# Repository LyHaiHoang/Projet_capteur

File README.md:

# Projet : Capteur Graphite à Crayon

## Table des matières
- [Projet : Capteur Graphite à Crayon](#projet--capteur-graphite-à-crayon)
  - [Table des matières](#table-des-matières)
- [Contexte](#contexte)
- [Réalisation du projet](#réalisation-du-projet)
  - [1. Matériaux utilisés](#1-matériaux-utilisés)
  - [2. Simulation électronique en utilisant LTSpice](#2-simulation-électronique-en-utilisant-ltspice)
    - [2.1 Fonctionnalité de condition nominale](#21-fonctionnalité-de-condition-nominale)
    - [2.2 Modélisation du capteur](#22-modélisation-du-capteur)
    - [2.3 Résultats visuels](#23-résultats-visuels)
    - [2.4 Simulation du signal alternatif](#24-simulation-du-signal-alternatif)
  - [3. Conception du circuit PCB en utilisant KiCad](#3-conception-du-circuit-pcb-en-utilisant-kicad)
    - [3.1 Réalisation des symboles et empreintes](#31-réalisation-des-symboles-et-empreintes)
    - [3.2 Réalisation du schéma électronique](#32-réalisation-du-schéma-électronique)
    - [3.3 Réalisation du PCB](#33-réalisation-du-pcb)
  - [4. Code Arduino](#4-code-arduino)
  - [5. Application Android codée avec MIT App Inventor](#5-application-android-codée-avec-mit-app-inventor)
    - [5.1. Initialisation](#51-initialisation)
    - [5.2. Composantes dans l'interface](#52-composantes-dans-linterface)
      - [Connection du Bluetooth:](#connection-du-bluetooth)
    - [Le bouton pour le capteur industriel (FlexSensor) et le capteur graphite](#le-bouton-pour-le-capteur-industriel-flexsensor-et-le-capteur-graphite)
    - [Le bouton "Mesure"](#le-bouton-mesure)
    - [Le bouton "Reset"](#le-bouton-reset)
    - [Bloc principal - Timer](#bloc-principal---timer)
    - [Le Graphique](#le-graphique)
  - [6. Réalisation du Shield](#6-réalisation-du-shield)
  - [7. Banc de test](#7-banc-de-test)
    - [7.1 Physique derrière le capteur en graphite](#71-physique-derrière-le-capteur-en-graphite)
    - [7.2 Résultats de mesures](#72-résultats-de-mesures)
  - [8. Datasheet](#8-datasheet)
- [Conclusion](#conclusion)
- [Références](#références)
- [Contacts](#contacts)
  - [Étudiants](#étudiants)
  - [Enseignants](#enseignants)

---

# Contexte
Ce projet vise à développer un capteur basé sur du graphite de crayon de papier pour des applications en instrumentation. L'objectif est d'explorer les propriétés conductrices du graphite et de les exploiter dans un circuit électronique interactif.

---

# Réalisation du projet

---

## 1. Matériaux utilisés

Dans ce projet, nous utilisons des composants électroniques et des modules disponibles dans la salle d'instrumentation avec une carte Arduino UNO. Tous les composants sont listés ci-dessous :
   * 1 carte Arduino UNO Rev 3
   * 1 module Bluetooth (HC-05)
   * 1 encodeur rotatif (Keyes KY-040)
   * 1 écran OLED (SSD 1306)
   * 1 capteur de flexion commercial (LLC 1070)
   * 1 capteur en graphite fait à l'aide de la mine d'un crayon de papier
   * 1 amplificateur de transimpédance (LTC1050)
   * 1 potentiomètre numérique (MCP41100)
   * 2 supports IC pour le potentiomètre et l'amplificateur
   * 1 résistance 1kΩ, 1 résistance 10kΩ, 2 résistances 100kΩ
   * 3 condensateurs 100nF, 1 condensateur 1µF

---

## 2. Simulation électronique en utilisant LTSpice

### 2.1 Fonctionnalité de condition nominale

Le courant d’entrée Isens varie entre 50 nA et 100 nA, ce qui entraîne une variation de la tension Vep appliquée à l’entrée non-inverseur V+ du LTC1050, entre 5 mV et 10 mV.

Le gain de l’amplificateur du LTC1050 est défini par : G = 1 + R3/R2 = 101. Par conséquent, la valeur de la tension de sortie du LTC1050 varie entre 0.5 V et 1 V.

Au départ, le signal exprimé en décibels est de 140 dB, ce qui correspond à :  
20 log(VADC / Isens).

Le microcontrôleur utilisé est un Arduino UNO, basé sur un microcontrôleur AVR avec une fréquence d’échantillonnage maximale fech = 200 kHz.  
Comme la conversion analogique-numérique se fait sur 13 bits, la fréquence d’échantillonnage réelle est limitée à 15.4 kHz.

D'après le théorème de Nyquist, la fréquence maximale du signal que l'on peut correctement numériser doit donc être inférieure à la moitié de cette valeur :  
fsignal < fech/2 = 7.7 kHz.

### 2.2 Modélisation du capteur

Le bruit à 50 Hz, généré notamment par l'écran TFT (bruit de type secteur), est clairement observé dans le spectre du signal. Pour l’atténuer, on agit sur le condensateur C4 du filtre passe-bas.

- Lorsque la valeur de C4 est augmentée à 10 µF, le pic de bruit à 50 Hz est fortement réduit, ce qui indique une amélioration de l’atténuation dans les basses fréquences.

- En revanche, si on diminue la valeur de C4, le bruit augmente, montrant que la fréquence de coupure du filtre remonte et que le bruit secteur passe plus facilement.

### 2.3 Résultats visuels

Une photo démontrant que notre circuit permet une amplification efficace du signal délivré par le capteur :

### 2.4 Simulation du signal alternatif

Ensuite, on présente la réponse du circuit lorsque l'on simule un courant alternatif, afin de vérifier que le bruit est correctement filtré :

Le bruit du réseau est atténué d'environ 72 dB à 50 Hz.

---

## 3. Conception du circuit PCB en utilisant KiCad

Afin de concevoir le circuit électronique, le logiciel en libre accès KICAD a été utilisé. L'ensemble des fichiers KiCad est disponible dans le dossier [Capteur_KICAD](./Capteur_KICAD).

### 3.1 Réalisation des symboles et empreintes

Pour commencer notre PCB (Printed Circuit Board), il est nécessaire de créer les symboles et les empreintes des composants qui ne sont pas disponibles dans la bibliothèque de KiCad. Nous avons réalisé les symboles du module Bluetooth, de l'encodeur rotatif, de l'écran OLED, du capteur de flexion et du capteur en graphite, afin de les ajouter au schéma de connexion. Ensuite, ces symboles ont été associés à une empreinte trouvée sur des sites de libre téléchargement.

### 3.2 Réalisation du schéma électronique

Ensuite, le schéma électronique est à construire. Dans cette partie, les différentes connexions entre composants sont définies et les pins de la carte Arduino sont attribués à chacun des composants.

### 3.3 Réalisation du PCB

L'objectif ici était d'allouer un branchement sur les entrées d'une carte Arduino UNO à chaque module. Nous avons aussi pour but de faire le moins possible de via (pont traversant permettant de chavaucher un routage).
Le circuit imprimé a été dessiné avec une attention particulière portée à la disposition des pistes pour minimiser les couplages parasites et faciliter le routage manuel.

Les contraintes de branchement ont été les suivantes:
  * Encoder: pin clk -> pin 2 (Arduino)
  * Bluetooth: pin TXD -> la pin 5 (pin RXD de l'Arduino)
               pin RXD -> la pin 6 (pin TXD de l'Arduino)
  * Potentiomètre digital: pin SCK -> pin 13 (pin SCK de l'Arduino)
                           pin SDI -> pin 11 ()
  * FlexSensor: sur une pin analogue (A2 choisi)
  * Capteur Graphite: sur une pin analogue (A0 choisi)

Ensuite, l'impression du circuit s'est ensuite faite par méthode chimie:
  * Plaque de cuivre/résine dont la face en cuivre est enduite d'une résine photosensible;
  * Insolation de la résine sur les parties du cuivre non voulue;
  * Attaque chimique dans un bain révélateur;
  * Rinçage du circuit;

---

## 4. Code Arduino

Le code Arduino permet de lire les valeurs du capteur en graphite, de gérer l'affichage d'un Menu sur l'écran OLED, la communication par Bluetooth avec l'application Android (voir section [5. Application Android codée avec MIT App Inventor](#5.-Application-Android-codée-avec-MIT-App-Inventor)) et le contrôle via l'encodeur rotatif.
Le code arduino est disponible dans le dossier [Capteur_Arduino](./Capteur_Arduino).

---

## 5. Application Android codée avec MIT App Inventor

Une application mobile a été développée pour :
- Recevoir les données en Bluetooth,
- Afficher les mesures en temps réel,
- Interagir avec le capteur de manière intuitive.

### 5.1. Initialisation

  Nous avons déclaré les variables initiales utilisées dans le programme:

  Puis nous avons initialisé le programme:

### 5.2. Composantes dans l'interface
---
#### Connection du Bluetooth:

Le bouton « List_Connection » permet de sélectionner le module Bluetooth auquel on souhaite se connecter. Le bouton « Button_Disconnect » permet également de déconnecter le module Bluetooth sélectionné.

---

### Le bouton pour le capteur industriel (FlexSensor) et le capteur graphite

Ces bouton permet de choisir le capteur que l'on veut afficher leur valeurs.

---
### Le bouton "Mesure"

Ce bouton permet d'envoyer un message vers l'arduino via bluetooth pour lui demande de renvoyer les valeurs de resistances dependant le mode du capteur choisi.

---
### Le bouton "Reset"

Ce bouton permet de réinitialiser le graph.

---
### Bloc principal - Timer

Pour pouvoir récupérer automatiquement des données, on commande séquentiellement Arduino de nous evoyer les données. Pour cela, on utilise le composante "Clock"dans MIT. 

---
### Le Graphique

Le graphique montre le variation de résistance du capteur FlexSensor et du capteur graphite à chaque mesure.

## 6. Réalisation du Shield

Pour la réalisation du shield, nous avons manuellement soudé l'ensemble des modules arduino et composants électroniques (résistances, capacités, amplificateur opérationnel) au PCB imprimé. (voir section [3.4 Réalisation du PCB](#34-réalisation-du-pcb)).

Le Shield réalisé intègre un amplificateur de signal LTC1050 pour amplifier les faibles signaux des capteurs avec précision, un encodeur rotatif permettant de naviguer dans le menu et de modifier les valeurs de résistance via un potentiomètre, un écran OLED pour afficher clairement les menus et les informations, ainsi qu’un module Bluetooth assurant la communication sans fil avec un téléphone portable pour le contrôle et la supervision à distance du système.

---

## 7. Banc de test

Afin de valider le fonctionnement du système, plusieurs tests ont été réalisés :
- Mesure des signaux et tensions aux bornes des capteurs et calcul de résistance.
- Test de communication Bluetooth.
- Et prise de mesures de résistance issues du capteur en graphite.

Un modèle 3D composé de fentes circulaires de différents rayons est utilisé pour le banc de test. En insérant le capteur dans ces fentes, une déformation est induite en fonction de son orientation (traction ou compression). La déformation est inversement proportionnelle au rayon des fentes circulaires, selon la relation suivante : ε = e / R

  Où :  
  - ε : déformation 
  - e : allongement imposé  
  - R : rayon de la fente (0,2 mm)

Ce système permet de contrôler précisément la déformation du capteur en choisissant simplement un rayon de fente spécifique.

### 7.1 Physique derrière le capteur en graphite

Une variation de la résistance du capteur est attendue lorsque ce dernier est déformé. Cette variation est notamment dû au rapprochement ou à l'éloignement des atomes de carbone.
Lorsque le capteur est mis en tension, les atomes de carbone ont tendance à s'écarter. Ainsi, moins d'atome sont en contact afin de créer une chaîne reliant les deux extrémités du cpateur. Les électrons passent plus difficilement, la résistance augmente donc.
Lorsque le capteur est mis en compression, les atomes de carbone se rapprochent. La configuration est plus favorable à la création de chaîne reliant les deux extrémités du capteur. Les électrons passent plus facilement, la résistance diminue donc.
Par ailleurs, il est attendu à ce que la résistance diminue en même temps que la dureté du crayon de papier augmente. Cela peut simplement s'expliquer par une réduction de la présence de carbone.

La résistance peut s'exprimer comme suivant:

  Où :
  - "l" la longueur de la couche de nanoparticule (graphite) ;
  - "a" le paramètre de maille de la matrice cubique centrée du graphite ;
  - "w" la largeur, et "d" l'épaisseur du film.
Quant à la résistance "R12", elle est obtenue en posant les équations de mécanique quantique appliquée à des nanoparticules :

Pour plus d'informations, les sources utilisées sont fournies dans la rubrique [Références](#références).

### 7.2 Résultats de mesures

Par la suite, nous avons caractérisé notre capteur en graphite afin de retrouver les résultats de l'étude dont la source est donnée ci-dessus. La tension aux bornes du capteur est mesurée, puis convertie en valeur de résistance. Cette valeur de résistance est affichée en fonction de la déformation appliquée sur le capteur.
Les graphiques ci-dessus montrent la variation relative de la valeur du capteur en fonction de la déformation dans deux modes : traction et compression. Des droites de régression linéaire passant par l’origine ont été tracées. Ces lignes théoriques démontrent que la valeur de ΔR/R₀ varie linéairement avec la déformation.

---

## 8. Datasheet
Les fiches techniques des principaux composants (LTC1050, HC-05, écran OLED, etc.) sont disponibles dans le dossier [datasheet_graphit_sensor.pdf](./Datasheet/datasheet_graphit_sensor.pdf) du projet. Par ailleurs, une documentation sur notre capteur graphite est disponible sur ce Github.

---

# Conclusion
Ce projet démontre la faisabilité d’un capteur à base de graphite de crayon pour des applications d’instrumentation. Le prototype final est capable de détecter des variations de résistance liées à la pression exercée sur le graphite. Néanmoins, la faible répétabilité des mesures et de la confection du capteur en graphite ne permet pas une industrialisation. On note aussi que durant le test, le graphite du capteur est en contact avec les parois. Cela pourrait engendrer un retrait de graphite à chaque insertion.
Les points d'amélioration pouvant être apportés sont : une amélioration du banc de test, la normalisation du dépôt de graphite.

Une documentation de notre capteur est aussi disponible ([Documentation Capteur Graphite](./Datasheet/Datasheet_graphit_sensor.pdf))

---

# Références
- Fiches techniques des composants (HC-05, Keyes KY-040, SSD 1306, LLC 1070, LTC1050, MCP41100)
- Documentation Arduino
- Tutoriels MIT App Inventor
- Outils de simulation LTSpice et KiCad

<ins>Sources sur l'étude du capteur en graphite :</ins>

"Pencil Drawn Strain Gauges and Chemiresistors on Paper
Cheng-Wei Lin*, Zhibo Zhao*, Jaemyung Kim & Jiaxing Huang
Department of Materials Science and Engineering,
Northwestern University 2220 Campus Drive, Evanston, IL, 60208, USA.
SCIENTIFIC REPORTS | 4 : 3812 | DOI: 10.1038/srep03812 - 2014"

"Electron transport in nanoparticle assemblies
K.-H. Müller1, J. Herrmann2, G. Wei1, B. Raguse1, and L.Wieczorek1
1Future Manufacturing Flagship, 1CSIRO Materials Science and Engineering
Lindfield NSW2070, Australia
2NationalMeasurement Institute, Lindfield NSW 2070, Australia
978-1-4244-5262-0/10/$26.00 © 2010 IEEE - ICONN 2010"

"Percolation model for electron conduction in films of metal nanoparticles linked by organic molecules
K.-H. Müller,* J. Herrmann, B. Raguse, G. Baxter, and T. Reda
Commonwealth Scientific and Industrial Research Organization, Telecommunications and Industrial Physics,
Sydney 2070, Australia
PHYSICAL REVIEW B 66, 075417 (2002)"

---

# Contacts

## Étudiants
- **Yoann Lai Koun Sing** : laikouns@insa-toulouse.fr  
- **Viet Hoang Pham** : vpham@insa-toulouse.fr  
- **Ly Hai Hoang** : lhoang@insa-toulouse.fr  

## Enseignants
- **Jérémie Grisolia** : jeremie.grisolia@insa-toulouse.fr  
- **Arnauld Biganzoli** : arnauld.biganzoli@insa-toulouse.fr  
- **Cathy Crouzet** : crouzet@insa-toulouse.fr  
- **Benjamin Mestre** : benjamin.mestre@scalian.com

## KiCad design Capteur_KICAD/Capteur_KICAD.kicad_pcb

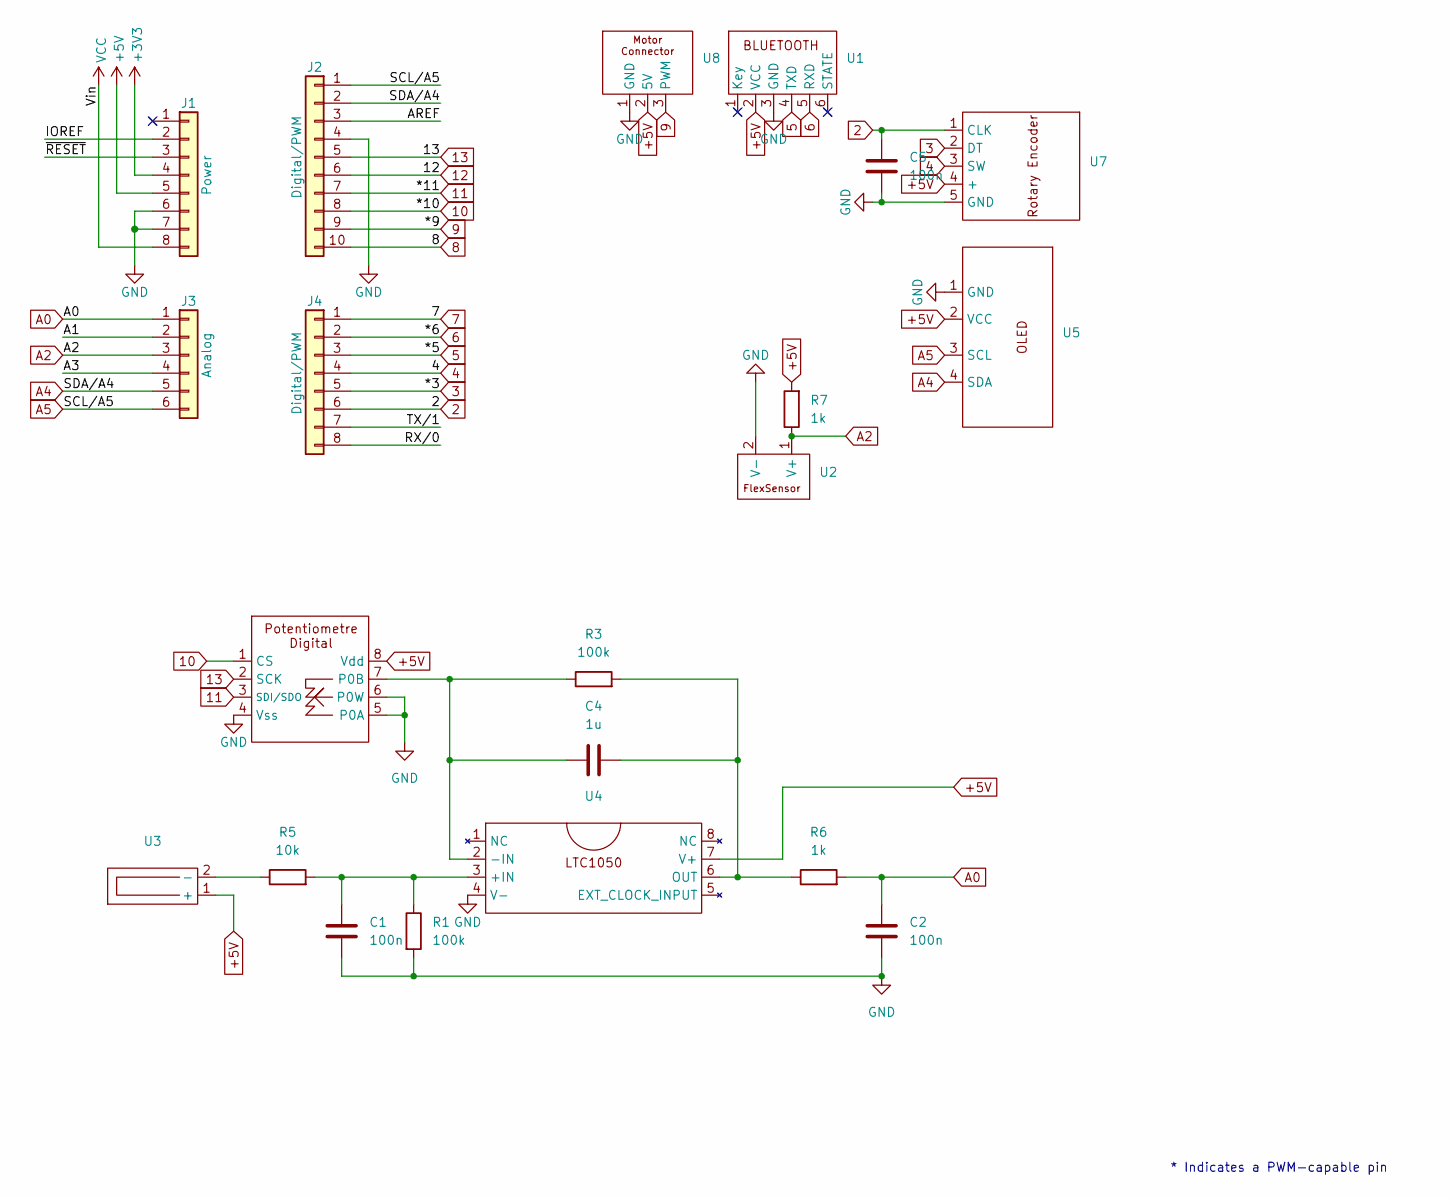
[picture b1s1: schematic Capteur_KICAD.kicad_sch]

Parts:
C1, C2, C5: 100n; C_Disc_D4.3mm_W1.9mm_P5.00mm
C4: 1u; C_Rect_L7.0mm_W4.5mm_P5.00mm
J1: Power; PinSocket_1x08_P2.54mm_Vertical
J2: Digital/PWM; PinSocket_1x10_P2.54mm_Vertical
J3: Analog; PinSocket_1x06_P2.54mm_Vertical
J4: Digital/PWM; PinSocket_1x08_P2.54mm_Vertical
R1, R3: 100k; R_Axial_DIN0204_L3.6mm_D1.6mm_P5.08mm_Horizontal
R5: 10k; R_Axial_DIN0204_L3.6mm_D1.6mm_P5.08mm_Horizontal
R6: 1k; R_Axial_DIN0207_L6.3mm_D2.5mm_P7.62mm_Horizontal
R7: 1k; R_Axial_DIN0204_L3.6mm_D1.6mm_P5.08mm_Horizontal
U1: Empreinte_Bluetooth
U2: Empreinte_FlexSensor
U3: Empreinte_GraphiteSensor
U4: PDIP-8_N
U5: Empreinte_OLED
U6: Empreinte_PotentiometreDigital
U7: Empreinte_Rotary_Encoder
U8: Empreinte_ConnecteurMoteur

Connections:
2: C5.1, J4.6, U7.1 (CLK)
3: J4.5, U7.2 (DT)
4: J4.4, U7.3 (SW)
5: J4.3, U1.4 (TXD)
6: J4.2, U1.5 (RXD)
7: J4.1
8: J2.10
9: J2.9, U8.3 (PWM)
10: J2.8, U6.1 (CS)
11: J2.7, U6.3 (SDI/SDO)
12: J2.6
13: J2.5, U6.2 (SCK)
+3V3: J1.4
+5V: J1.5, R7.2, U1.2 (VCC), U3.1 (+), U4.7 (V+), U5.2 (VCC), U6.8 (Vdd), U7.4 (+), U8.2 (5V)
/A1: J3.2
/A3: J3.4
/AREF: J2.3
/IOREF: J1.2
/RX/0: J4.8
/TX/1: J4.7
/~RESET: J1.3
A0: C2.2, J3.1, R6.2
A2: J3.3, R7.1, U2.1 (V+)
A4: J2.2, J3.5, U5.4 (SDA)
A5: J2.1, J3.6, U5.3 (SCL)
GND: C1.1, C2.1, C5.2, J1.6, J1.7, J2.4, R1.2, U1.3 (GND), U2.2 (V-), U4.4 (V-), U5.1 (GND), U6.4 (Vss), U6.5 (P0A), U6.6 (P0W), U7.5 (GND), U8.1 (GND)
unnamed: R5.1, U3.2 (-)
unnamed: C1.2, R1.1, R5.2, U4.3 (+IN)
unnamed: C4.1, R3.1, U4.2 (-IN), U6.7 (P0B)
unnamed: C4.2, R3.2, R6.1, U4.6 (OUT)
VCC: J1.8

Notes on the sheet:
* Indicates a PWM-capable pin

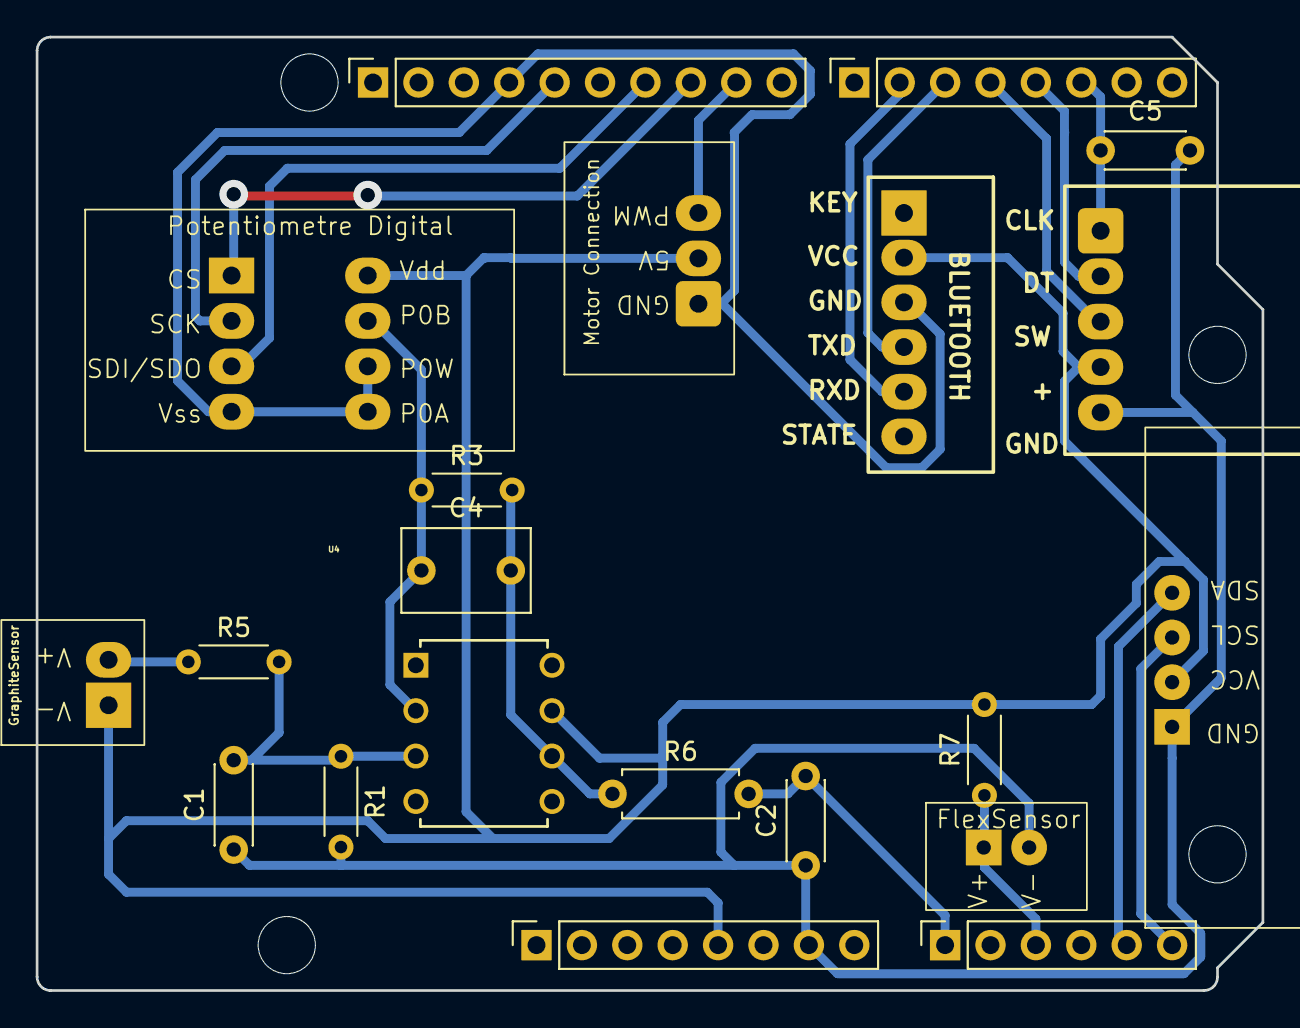
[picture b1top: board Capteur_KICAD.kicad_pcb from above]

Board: 2 copper layers, 68.6 x 53.3 mm, 25 parts (0 on the bottom side), 19 nets.

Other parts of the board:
MH1, MH2, MH3, MH4: MountingHole_3.2mm

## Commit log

2025-03-13 Transfert KICAD avec schématique et PCB
2025-03-13 add LTSpice and datasheet
2025-03-13 Librairie d'Empreintes
2025-03-17 Updating PCB, proposition of final PCB
2025-03-17 Adding Arduino file for coding
2025-03-17 Initialisation of OLED Screen
2025-03-17 Updating PCB on KiCad, final proposition without 3D model
2025-03-18 Updating PCB, adding 3D models and correcting minor error on routing
2025-03-19 Pin shape correction
2025-03-25 Code structuration
2025-03-28 add file datasheet
2025-03-30 Building Menu (Rotary encoder and OLED screen)
2025-03-30 Add flex capteur and bluetooth functions
2025-05-10 Menu Cpateur + bluetooth
2025-05-13 Correction
2025-05-13 datasheet
2025-05-13 debbugging Menu and capteur
2025-05-14 Functionnal Menu and Sensor Work to do: Bluetooth
2025-05-14 ltcsipce
2025-05-15 implementing Bluetooth
2025-05-15 Program for mesuring the resistance of the Graphite sensor
2025-05-15 Building README
2025-05-15 ltspice
2025-05-15 ltspice test
2025-05-15 add image and readme ltspice
2025-05-15 modify reference image
2025-05-15 modify readme
2025-05-15 add image
2025-05-15 add banc de test
2025-05-16 Add interface
2025-05-17 Fixing Bluetooth connection
2025-05-18 Data Mesure of Graphite Sensor
2025-05-18 Code organisation
2025-05-19 Taking mesure
2025-05-19 Try to fix bluetooth
2025-05-20 banc test 6B
2025-05-20 test
2025-05-21 measure
2025-05-21 README
2025-05-21 README, Banc de test
2025-05-21 Add code and application
2025-05-28 add interface and remane
2025-05-28 Enrichissement du readme
2025-05-28 modify datasheet
2025-05-28 add datasheet pdf
2025-05-29 Modification of README
2025-05-29 Readme: ajout texte partie 3.
2025-05-29 readme modify
2025-05-29 add readme
2025-05-29 Add comments on Arduino code
2025-05-29 Readme: modification partie 4 Ajout d'images
2025-05-29 Readme: Correction d'erreur
2025-05-29 Add MIT part
2025-05-29 Readme: modification
2025-05-29 Image GUI android
2025-05-29 Ajout présentation du projet capteur
2025-05-29 Finish MIT part Arrange image
2025-05-29 Finish MIT
2025-05-29 Delere unnecessary image
2025-05-29 Fix problem about image in MIT
2025-05-29 Correction README et nom de schéma
2025-05-29 corrections affichage images
2025-05-29 correction affichage images
